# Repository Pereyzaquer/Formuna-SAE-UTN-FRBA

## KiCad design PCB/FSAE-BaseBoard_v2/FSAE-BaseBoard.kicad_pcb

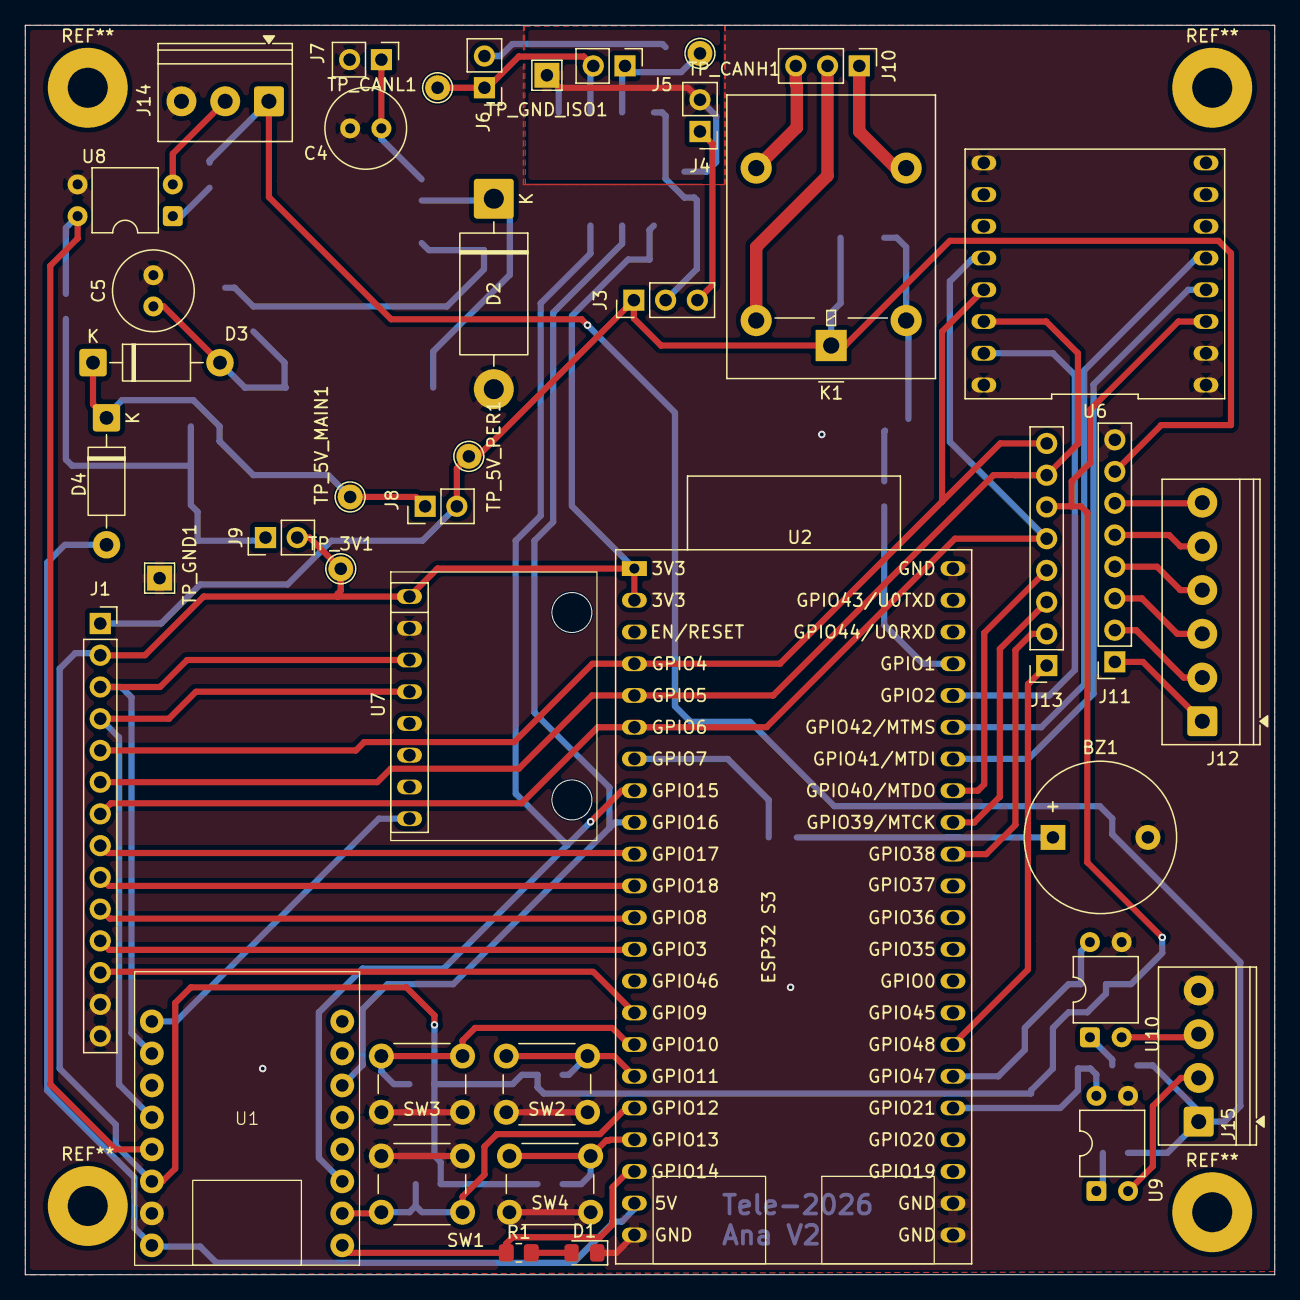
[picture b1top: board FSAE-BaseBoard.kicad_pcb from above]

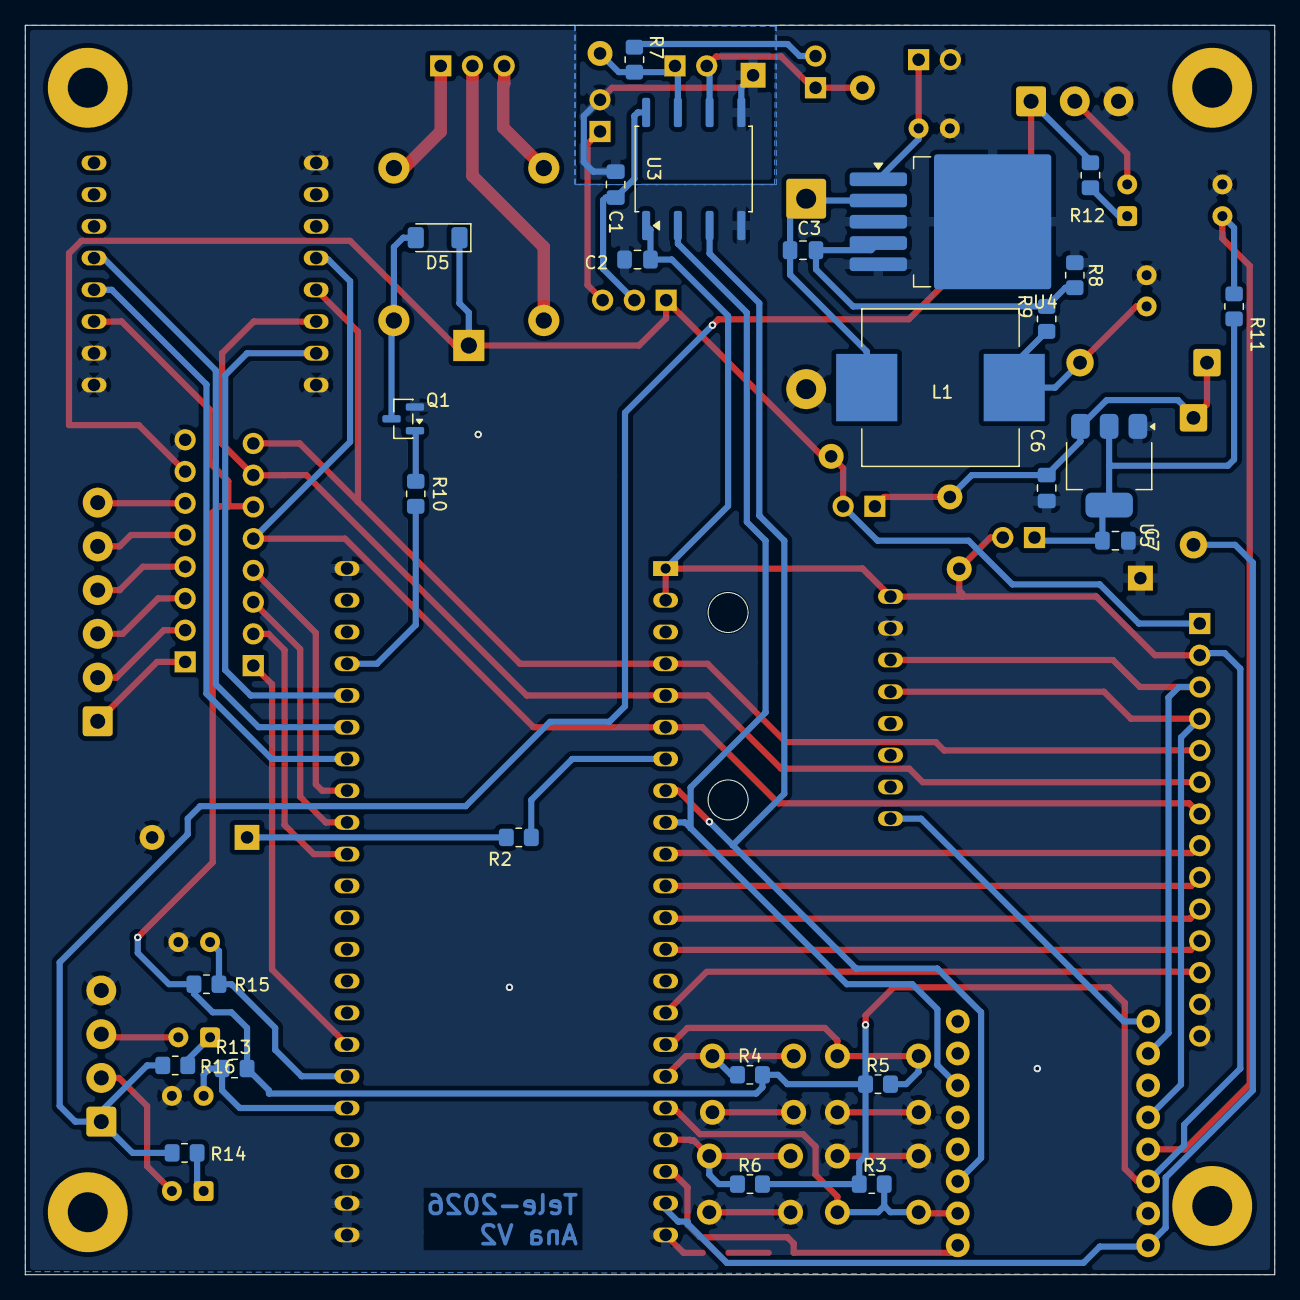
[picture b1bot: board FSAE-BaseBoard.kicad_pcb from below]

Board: 2 copper layers, 100.0 x 100.0 mm, 67 parts (26 on the bottom side), 65 nets.

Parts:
BZ1: Buzzer; Buzzer_12x9.5RM7.6
C1, C2: 100nF; C_0805_2012Metric_Pad1.18x1.45mm_HandSolder
C3: 15nF; C_0805_2012Metric_Pad1.18x1.45mm_HandSolder
C4: 100uF; C_Radial_D6.3mm_H11.0mm_P2.50mm
C5: 220uF; C_Radial_D6.3mm_H11.0mm_P2.50mm
C6, C7: 10uF; C_0805_2012Metric_Pad1.18x1.45mm_HandSolder
D1: LED; LED_0805_2012Metric_Pad1.15x1.40mm_HandSolder
D2: 1N5822; D_DO-201AD_P15.24mm_Horizontal
D3, D4: 1N5819; D_DO-41_SOD81_P10.16mm_Horizontal
D5: LL4148; D_MiniMELF
J1: Conn_01x14_Socket; PinSocket_1x14_P2.54mm_Vertical
J3, J10: Conn_01x03; PinHeader_1x03_P2.54mm_Vertical
J4, J5, J6, J7, J8, J9: Conn_01x02; PinHeader_1x02_P2.54mm_Vertical
J11, J13: Zocalo_Resolver; PinSocket_1x08_P2.54mm_Vertical
J12: Bornera_Resolver; TerminalBlock_Phoenix_PT-1,5-6-3.5-H_1x06_P3.50mm_Horizontal
J14: Screw_Terminal_01x03; TerminalBlock_Phoenix_PT-1,5-3-3.5-H_1x03_P3.50mm_Horizontal
J15: Bornera_Encoder; TerminalBlock_Phoenix_PT-1,5-4-3.5-H_1x04_P3.50mm_Horizontal
K1: Relay_SPDT; Relay_SPDT_Omron-G5LE-1
L1: 33uH; L_Wuerth_WE-PD-Typ-LS_Handsoldering
Q1: BC817; SOT-23
R1: 1k; R_0805_2012Metric_Pad1.20x1.40mm_HandSolder
R2: 100; R_0805_2012Metric_Pad1.20x1.40mm_HandSolder
R3, R4, R5, R6: 10k; R_0805_2012Metric_Pad1.20x1.40mm_HandSolder
R7: 120; R_0805_2012Metric_Pad1.20x1.40mm_HandSolder
R8, R10: 1K; R_0805_2012Metric_Pad1.20x1.40mm_HandSolder
R9: 3K1; R_0805_2012Metric_Pad1.20x1.40mm_HandSolder
R11, R13, R15: 10K; R_0805_2012Metric_Pad1.20x1.40mm_HandSolder
R12, R14, R16: 2K2; R_0805_2012Metric_Pad1.20x1.40mm_HandSolder
SW1, SW2, SW3, SW4: SW_Push; SW_PUSH_6mm_H5mm
TP_3V1, TP_5V_MAIN1, TP_5V_PER1: TestPoint; TestPoint_THTPad_D2.0mm_Drill1.0mm
TP_CANH1: TestPoint; TestPoint_THTPad_D2.0mm_Drill1.0mm
TP_CANL1: TestPoint; TestPoint_THTPad_D2.0mm_Drill1.0mm
TP_GND1: TestPoint; TestPoint_THTPad_2.0x2.0mm_Drill1.0mm
TP_GND_ISO1: TestPoint; TestPoint_THTPad_2.0x2.0mm_Drill1.0mm
U1: ESP32 C3; ESP32 C3 SM
U2: ESP32 S3
U3: ISO1050DUB; SOP-8_6.62x9.15mm_P2.54mm
U4: LM2596S-ADJ; TO-263-5_TabPin3
U5: AMS1117-3.3; SOT-223-3_TabPin2
U6: LoRa SX1278; LoRa_SX178
U7: MPU 6050; MPU6050
U8, U9, U10: PC817; DIP-4_W7.62mm

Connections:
+3.3V: C2.1, C7.1, J1.2, J9.1, J9.2, J13.6, R3.1, R4.1, R5.1, R6.1, R11.1, R13.1, R15.1, TP_3V1.1 (1_1), U1.11 (3V3), U2.1 (VDD_3V3), U2.2 (VDD_3V3), U3.1 (VCC1), U5.2 (VO), U6.3 (3.3V), U7.1 (VCC)
+5V: D5.1 (K), J1.1, J3.1, J8.2, J11.7, K1.1, TP_5V_PER1.1 (1_1)
+5VA: C5.1, D3.2 (A), L1.1, R9.2
+12V: J14.1, J15.1, R12.1, R14.1, R16.1
/Bloque de Alimentacion/VIN_BAT: C4.1, J7.1, U4.1 (VIN)
/Bloque de Alimentacion/V_USB: D4.2 (A), U1.9 (5V), U2.21 (VDD_5V)
/Comunicacion CAN/CANH: J5.1, R7.1, TP_CANH1.1 (1_1), U3.7 (CANH)
/Comunicacion CAN/CANL: J5.2, J6.1, TP_CANL1.1 (1_1), U3.6 (CANL)
/Comunicacion CAN/RX: U1.3 (GPIO7/CS), U2.8 (GPIO15/RTC/U0RTS/ADC2_4), U3.3 (TXD)
/Comunicacion CAN/TX: U1.6 (GPIO10), U2.9 (GPIO16/RTC/U0CTS/ADC2_5), U3.2 (RXD)
/ESP32 C3 y S3/A0_MODE: J13.2, U2.35 (GPIO38/RGB_LED)
/ESP32 C3 y S3/A1_MODE: J13.1, U2.29 (GPIO48/SPICLK_N)
/ESP32 C3 y S3/ADC2_0: J1.10, U2.12 (GPIO8/RTC/TOUCH8/ADC1_7)
/ESP32 C3 y S3/ADC2_1: J1.11, U2.13 (GPIO3/RTC/TOUCH3/ADC1_2/JTAG)
/ESP32 C3 y S3/BTN_1: R3.2, SW1.1, U1.2 (GPIO6/MOSI), U2.18 (GPIO12/RTC/TOUCH12/ADC2_1)
/ESP32 C3 y S3/BTN_2: R4.2, SW2.1, U2.17 (GPIO11/RTC/TOUCH11/ADC2_0)
/ESP32 C3 y S3/BTN_3: R5.2, SW3.1, U2.16 (GPIO10/RTC/TOUCH10/ADC1_9)
/ESP32 C3 y S3/BTN_4: R6.2, SW4.1, U2.19 (GPIO13/RTC/TOUCH13/ADC2_2)
/ESP32 C3 y S3/CS_LORA: U2.40 (GPIO2/RTC/TOUCH2/ADC1_1), U6.15 (NSS)
/ESP32 C3 y S3/CS_RES: J13.4, U2.37 (GPIO40/MTDO/CLK_OUT2)
/ESP32 C3 y S3/CTRL_BUZZER: R2.1, U2.7 (GPIO7/RTC/TOUCH7/ADC1_6)
/ESP32 C3 y S3/CTRL_RELE: R10.1, U2.41 (GPIO1/RTC/TOUCH1/ADC1_0)
/ESP32 C3 y S3/ENC_A: R13.2, U2.27 (GPIO21/RTC), U9.4
/ESP32 C3 y S3/ENC_B: R15.2, U2.28 (GPIO47/SPICLK_P), U10.4
/ESP32 C3 y S3/GPIO3: J1.12, U2.15 (GPIO9/RTC/TOUCH9/ADC1_8)
/ESP32 C3 y S3/INT_LORA: U2.39 (GPIO42/MTMS), U6.5 (DIO0)
/ESP32 C3 y S3/INT_MPU: U1.16 (GPIO0/A0), U7.8 (INT)
/ESP32 C3 y S3/LED_ESTADO: R1.1, U1.1 (GPIO5/A5/MISO), U2.20 (GPIO14/RTC/TOUCH14/ADC2_3)
/ESP32 C3 y S3/MISO: J1.5, J13.8, U2.4 (GPIO4/RTC/TOUCH4/ADC1_3), U6.13 (MISO)
/ESP32 C3 y S3/MOSI: J1.6, J13.7, U2.5 (GPIO5/RTC/TOUCH5/ADC1_4), U6.14 (MOSI)
/ESP32 C3 y S3/RST_LORA: U2.38 (GPIO41/MTDI/CLK_OUT1), U6.4 (RST)
/ESP32 C3 y S3/SAMPLE: J13.3, U2.36 (GPIO39/MTCK/CLK_OUT3)
/ESP32 C3 y S3/SCK: J1.7, J13.5, U2.6 (GPIO6/RTC/TOUCH6/ADC1_5), U6.12 (SCK)
/ESP32 C3 y S3/SCL_MPU: J1.3, U1.15 (GPIO1/A1), U7.3 (SCL)
/ESP32 C3 y S3/SDA_MPU: J1.4, U1.13 (GPIO3/A3), U7.4 (SDA)
/ESP32 C3 y S3/SENSOR_RPM: R11.2, U1.12 (GPIO4/A4/SCK), U8.4
/ESP32 C3 y S3/UART1_RX: J1.9, U2.11 (GPIO18/RTC/U1RXD/ADC2_7/CLK_OUT3)
/ESP32 C3 y S3/UART1_TX: J1.8, U2.10 (GPIO17/RTC/U1TXD/ADC2_6)
/Perifericos/ENC_A_RAW: J15.2, U9.2
/Perifericos/ENC_B_RAW: J15.3, U10.2
/Perifericos/RES_COS_N: J11.6, J12.6
/Perifericos/RES_COS_P: J11.5, J12.5
/Perifericos/RES_EXC_N: J11.2, J12.2
/Perifericos/RES_EXC_P: J11.1, J12.1
/Perifericos/RES_SIN_N: J11.4, J12.4
/Perifericos/RES_SIN_P: J11.3, J12.3
/Perifericos/Señal_12V: J14.2, U8.2
GND: BZ1.2 (-), C2.2, C4.2, C5.2, C6.2, C7.2, D1.1 (K), D2.2 (A), J1.13, J1.14, J7.2, J11.8, J14.3, J15.4, Q1.2 (E), R8.1, SW1.2, SW2.2, SW3.2, SW4.2, TP_GND1.1 (1_1), U1.10 (GND), U2.22 (GND), U2.23 (GND), U2.24 (GND), U2.44 (GND), U3.4 (GND1), U4.3 (GND), U4.5 (~ON/OFF), U5.1 (GND), U6.1 (GND), U6.2 (GND), U6.9 (GND), U6.16 (GND), U7.2 (GND), U8.3, U9.3, U10.3
GND ISO: C1.2, J4.2, TP_GND_ISO1.1 (1_1), U3.5 (GND2)
unnamed: BZ1.1 (+), R2.2
unnamed: D1.2 (A), R1.2
unnamed: C3.2, D2.1 (K), L1.2, U4.2 (OUT)
unnamed: C6.1, D3.1 (K), D4.1 (K), J8.1, TP_5V_MAIN1.1 (1_1), U5.3 (VI)
unnamed: D5.2 (A), K1.2, Q1.3 (C)
unnamed: C1.1, J3.2, U3.8 (VCC2)
unnamed: J3.3, J4.1
unnamed: J6.2, R7.2
unnamed: J10.1, K1.3
unnamed: J10.2, K1.5
unnamed: J10.3, K1.4
unnamed: Q1.1 (B), R10.2
unnamed: R12.2, U8.1
unnamed: R14.2, U9.1
unnamed: R16.2, U10.1
unnamed: C3.1, R8.2, R9.1, U4.4 (FB)

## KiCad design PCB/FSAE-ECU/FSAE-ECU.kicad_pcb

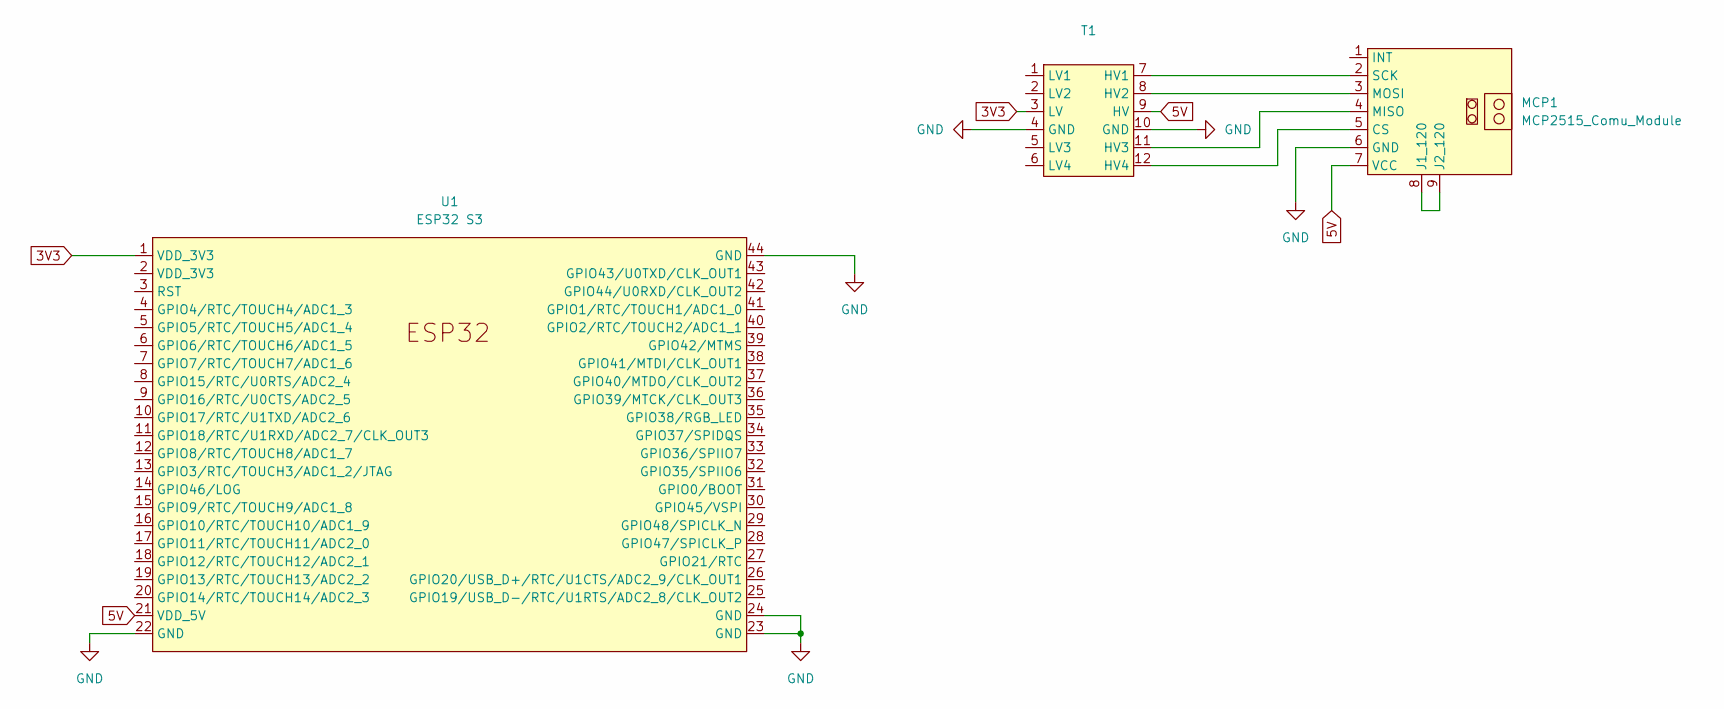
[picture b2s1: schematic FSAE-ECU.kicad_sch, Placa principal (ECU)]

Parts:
MCP1: MCP2515_Comu_Module; MCP2515_Comun_Module
T1: Conver_Logico
U1: ESP32 S3

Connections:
3V3: T1.3 (LV), U1.1 (VDD_3V3)
5V: MCP1.7 (VCC), T1.9 (HV), U1.21 (VDD_5V)
GND: MCP1.6 (GND), T1.4 (GND), T1.10 (GND), U1.22 (GND), U1.23 (GND), U1.24 (GND), U1.44 (GND)
unnamed: MCP1.4 (MISO), T1.11 (HV3)
unnamed: MCP1.5 (CS), T1.12 (HV4)
unnamed: MCP1.8 (J1_120), MCP1.9 (J2_120)
unnamed: MCP1.3 (MOSI), T1.8 (HV2)
unnamed: MCP1.2 (SCK), T1.7 (HV1)

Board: 2 copper layers, 3 parts (0 on the bottom side), 8 nets, no tracks yet.

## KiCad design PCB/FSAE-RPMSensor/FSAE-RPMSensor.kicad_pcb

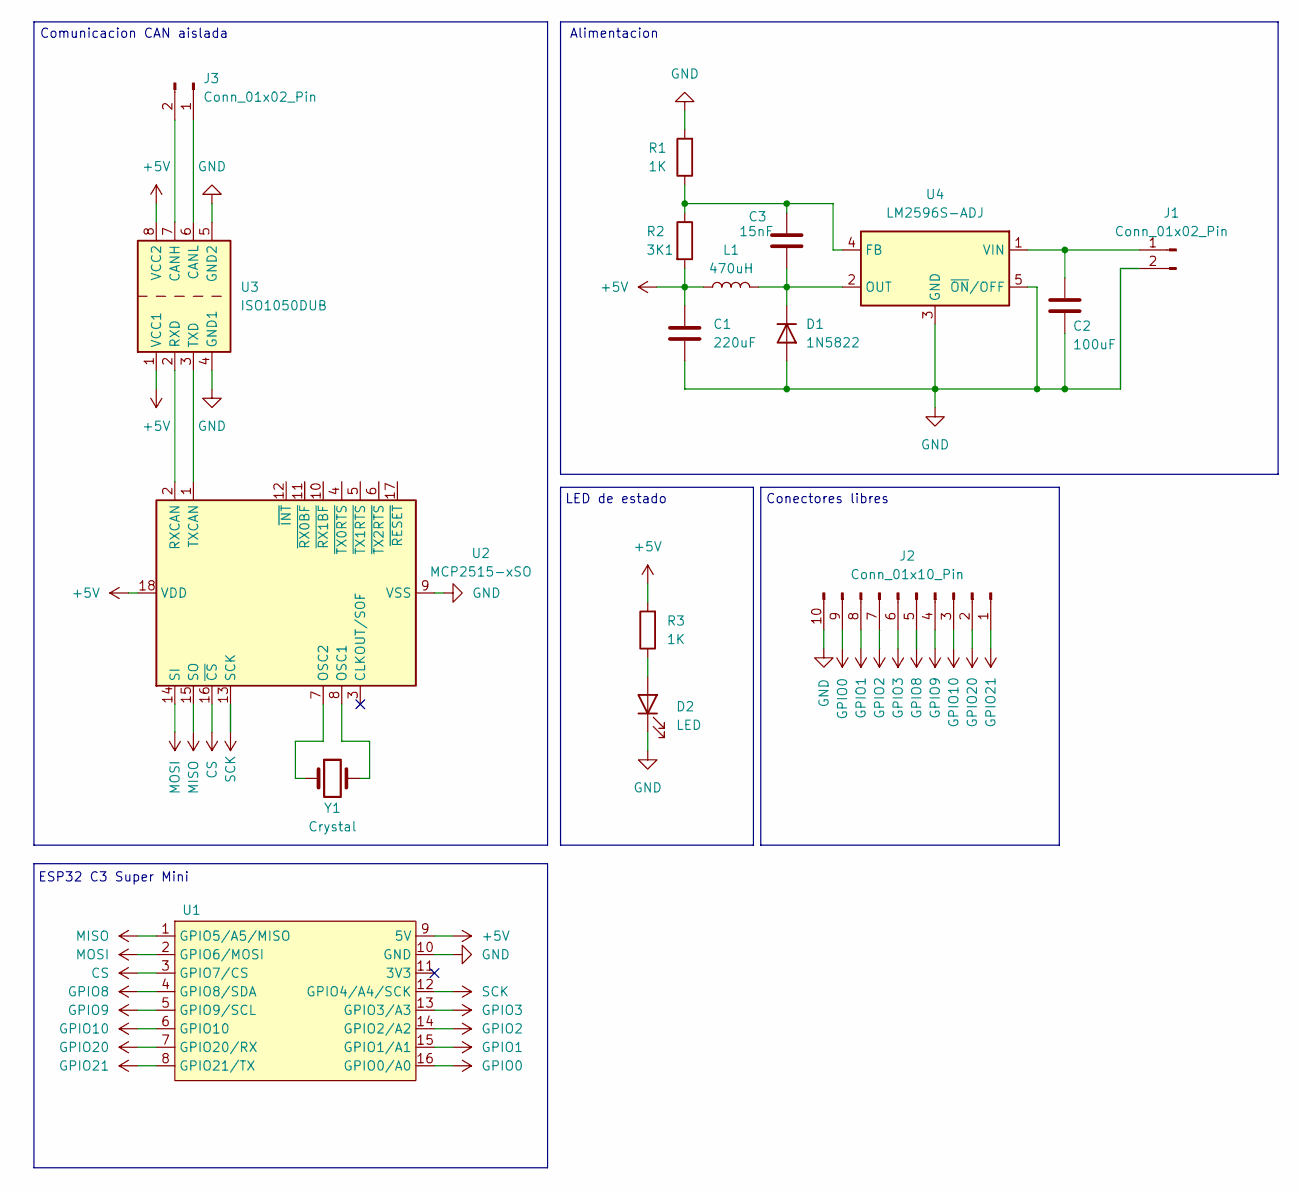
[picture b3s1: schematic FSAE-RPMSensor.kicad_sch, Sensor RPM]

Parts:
C1: 220uF; C_Elec_8x5.4
C2: 100uF; C_Elec_8x5.4
C3: 15nF; C_0603_1608Metric
D1: 1N5822; D_1206_3216Metric
D2: LED; D_0603_1608Metric
J1, J3: Conn_01x02_Pin; AMASS_XT30U-F_1x02_P5.0mm_Vertical
J2: Conn_01x10_Pin; PinHeader_1x10_P1.00mm_Vertical
L1: 470uH; L_10.4x10.4_H4.8
R1, R3: 1K; R_0603_1608Metric
R2: 3K1; R_0603_1608Metric
U1: ESP32 C3 SM
U2: MCP2515-xSO; SOIC-18W_7.5x11.6mm_P1.27mm
U3: ISO1050DUB; SOP-8_6.62x9.15mm_P2.54mm
U4: LM2596S-ADJ; TO-263-5_TabPin3
Y1: Crystal; Crystal_HC18-U_Vertical

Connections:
+5V: C1.1, L1.1, R2.2, R3.2, U1.9 (5V), U2.18 (VDD), U3.1 (VCC1), U3.8 (VCC2)
CS: U1.3 (GPIO7/CS), U2.16 (~CS)
GND: C1.2, C2.2, D1.2 (A), D2.1 (K), J1.2, J2.10, R1.2, U1.10 (GND), U2.9 (VSS), U3.4 (GND1), U3.5 (GND2), U4.3 (GND), U4.5 (~ON/OFF)
GPIO0: J2.9, U1.16 (GPIO0/A0)
GPIO1: J2.8, U1.15 (GPIO1/A1)
GPIO2: J2.7, U1.14 (GPIO2/A2)
GPIO3: J2.6, U1.13 (GPIO3/A3)
GPIO8: J2.5, U1.4 (GPIO8/SDA)
GPIO9: J2.4, U1.5 (GPIO9/SCL)
GPIO10: J2.3, U1.6 (GPIO10)
GPIO20: J2.2, U1.7 (GPIO20/RX)
GPIO21: J2.1, U1.8 (GPIO21/TX)
MISO: U1.1 (GPIO5/A5/MISO), U2.15 (SO)
MOSI: U1.2 (GPIO6/MOSI), U2.14 (SI)
unnamed: C3.2, D1.1 (K), L1.2, U4.2 (OUT)
unnamed: D2.2 (A), R3.1
unnamed: C2.1, J1.1, U4.1 (VIN)
unnamed: J3.1, U3.6 (CANL)
unnamed: J3.2, U3.7 (CANH)
unnamed: U2.8 (OSC1), Y1.2
unnamed: U2.7 (OSC2), Y1.1
unnamed: U2.2 (RXCAN), U3.2 (RXD)
unnamed: U2.1 (TXCAN), U3.3 (TXD)
unnamed: C3.1, R1.1, R2.1, U4.4 (FB)
SCK: U1.12 (GPIO4/A4/SCK), U2.13 (SCK)

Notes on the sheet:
ESP32 C3 Super Mini
Comunicacion CAN aislada
Conectores libres
LED de estado
Alimentacion

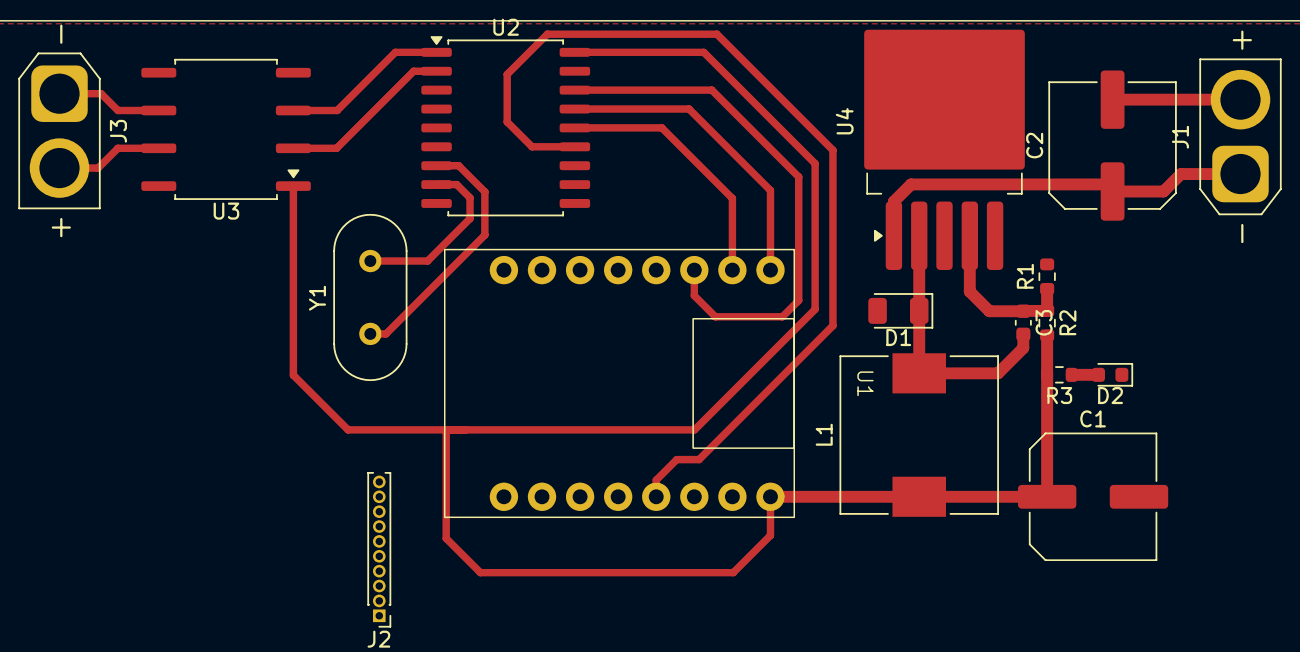
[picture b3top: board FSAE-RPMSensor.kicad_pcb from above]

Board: 2 copper layers, 17 parts (0 on the bottom side), 25 nets.
